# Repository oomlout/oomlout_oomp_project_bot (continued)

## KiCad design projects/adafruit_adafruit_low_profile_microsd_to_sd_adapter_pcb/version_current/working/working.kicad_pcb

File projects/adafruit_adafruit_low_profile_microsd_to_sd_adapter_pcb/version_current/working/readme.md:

# OOMP Project  
## Adafruit-Low-profile-microSD-to-SD-Adapter-PCB  by adafruit  
  
oomp key: oomp_projects_flat_adafruit_adafruit_low_profile_microsd_to_sd_adapter_pcb  
(snippet of original readme)  
  
-- Adafruit Low profile microSD to SD Adapter PCB (discontinued)  
<a href="http://www.adafruit.com/products/966"><br/>  
Click here to view on the Adafruit website  
</a>  
  
PCB files for the Adafruit Low-profile microSD to SD Adapter. Format is EagleCAD schematic and board layout  
- https://www.adafruit.com/product/966  
  
This product has been discontinued.  
  
--- License  
  
Adafruit invests time and resources providing this open source design, please support Adafruit and open-source hardware by purchasing products from [Adafruit.com](https://www.adafruit.com)!  
  
Creative Commons Attribution, Share-Alike license, check license.txt for more information All text above must be included in any redistribution -   
See license.txt for more information.  
  
  full source readme at [readme_src.md](readme_src.md)  
  
source repo at: [https://github.com/adafruit/Adafruit-Low-profile-microSD-to-SD-Adapter-PCB](https://github.com/adafruit/Adafruit-Low-profile-microSD-to-SD-Adapter-PCB)  
## Board  

## Schematic  

[schematic pdf](working_schematic.pdf)  
## Images

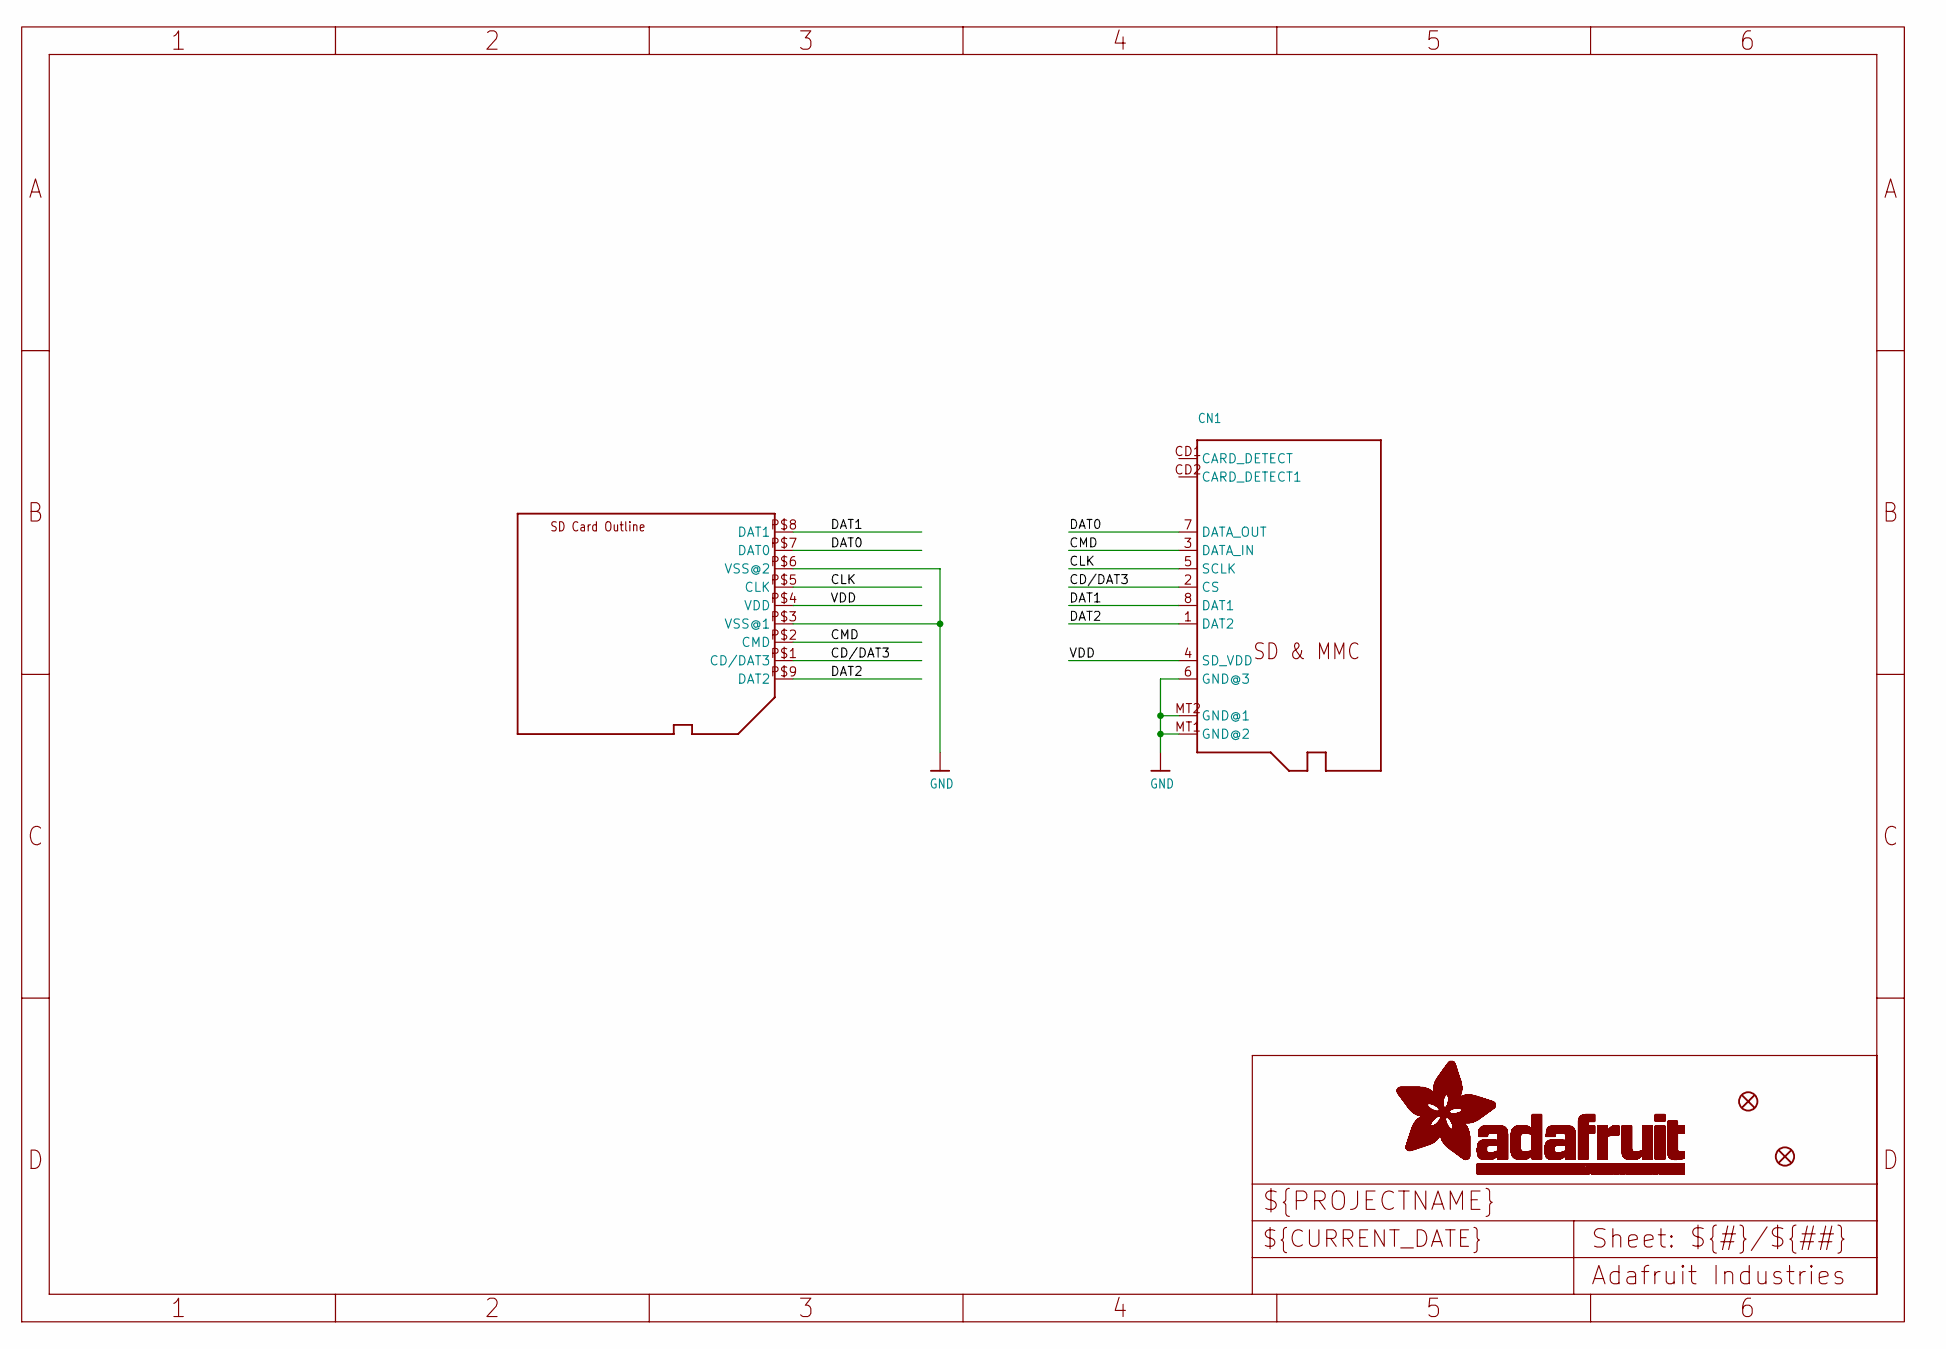
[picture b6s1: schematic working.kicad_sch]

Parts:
CN1: MICROSD
FID1, FID2: FIDUCIAL1X2.5; FIDUCIAL-1X2.5
U$2: SDCARD_PCBCARRIERTDOCU; SDCARD_PCBCARRIER_DOCU

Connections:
CD/DAT3: CN1.2 (CS), U$2.P$1 (CD/DAT3)
CLK: CN1.5 (SCLK), U$2.P$5 (CLK)
CMD: CN1.3 (DATA_IN), U$2.P$2 (CMD)
DAT0: CN1.7 (DATA_OUT), U$2.P$7 (DAT0)
DAT1: CN1.8 (DAT1), U$2.P$8 (DAT1)
DAT2: CN1.1 (DAT2), U$2.P$9 (DAT2)
GND: CN1.6 (GND@3), CN1.MT1 (GND@2), CN1.MT2 (GND@1), U$2.P$3 (VSS@1), U$2.P$6 (VSS@2)
VDD: CN1.4 (SD_VDD), U$2.P$4 (VDD)

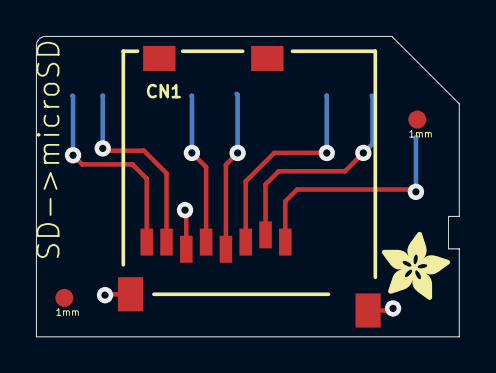
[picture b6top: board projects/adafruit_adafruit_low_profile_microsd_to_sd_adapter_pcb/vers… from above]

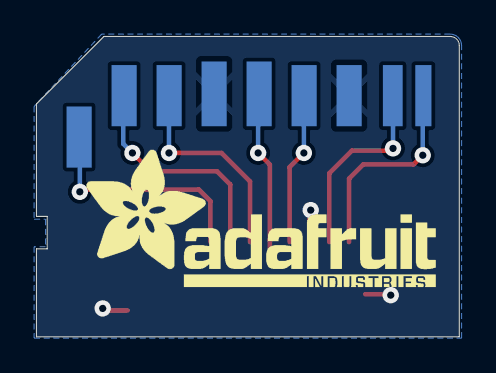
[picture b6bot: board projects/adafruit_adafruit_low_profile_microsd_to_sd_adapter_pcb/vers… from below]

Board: 2 copper layers, 23.5 x 16.7 mm, 6 parts (2 on the bottom side), 8 nets.

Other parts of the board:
U$5: ADAFRUIT_3.5MM
U$6: ADAFRUIT_TEXT_20MM
